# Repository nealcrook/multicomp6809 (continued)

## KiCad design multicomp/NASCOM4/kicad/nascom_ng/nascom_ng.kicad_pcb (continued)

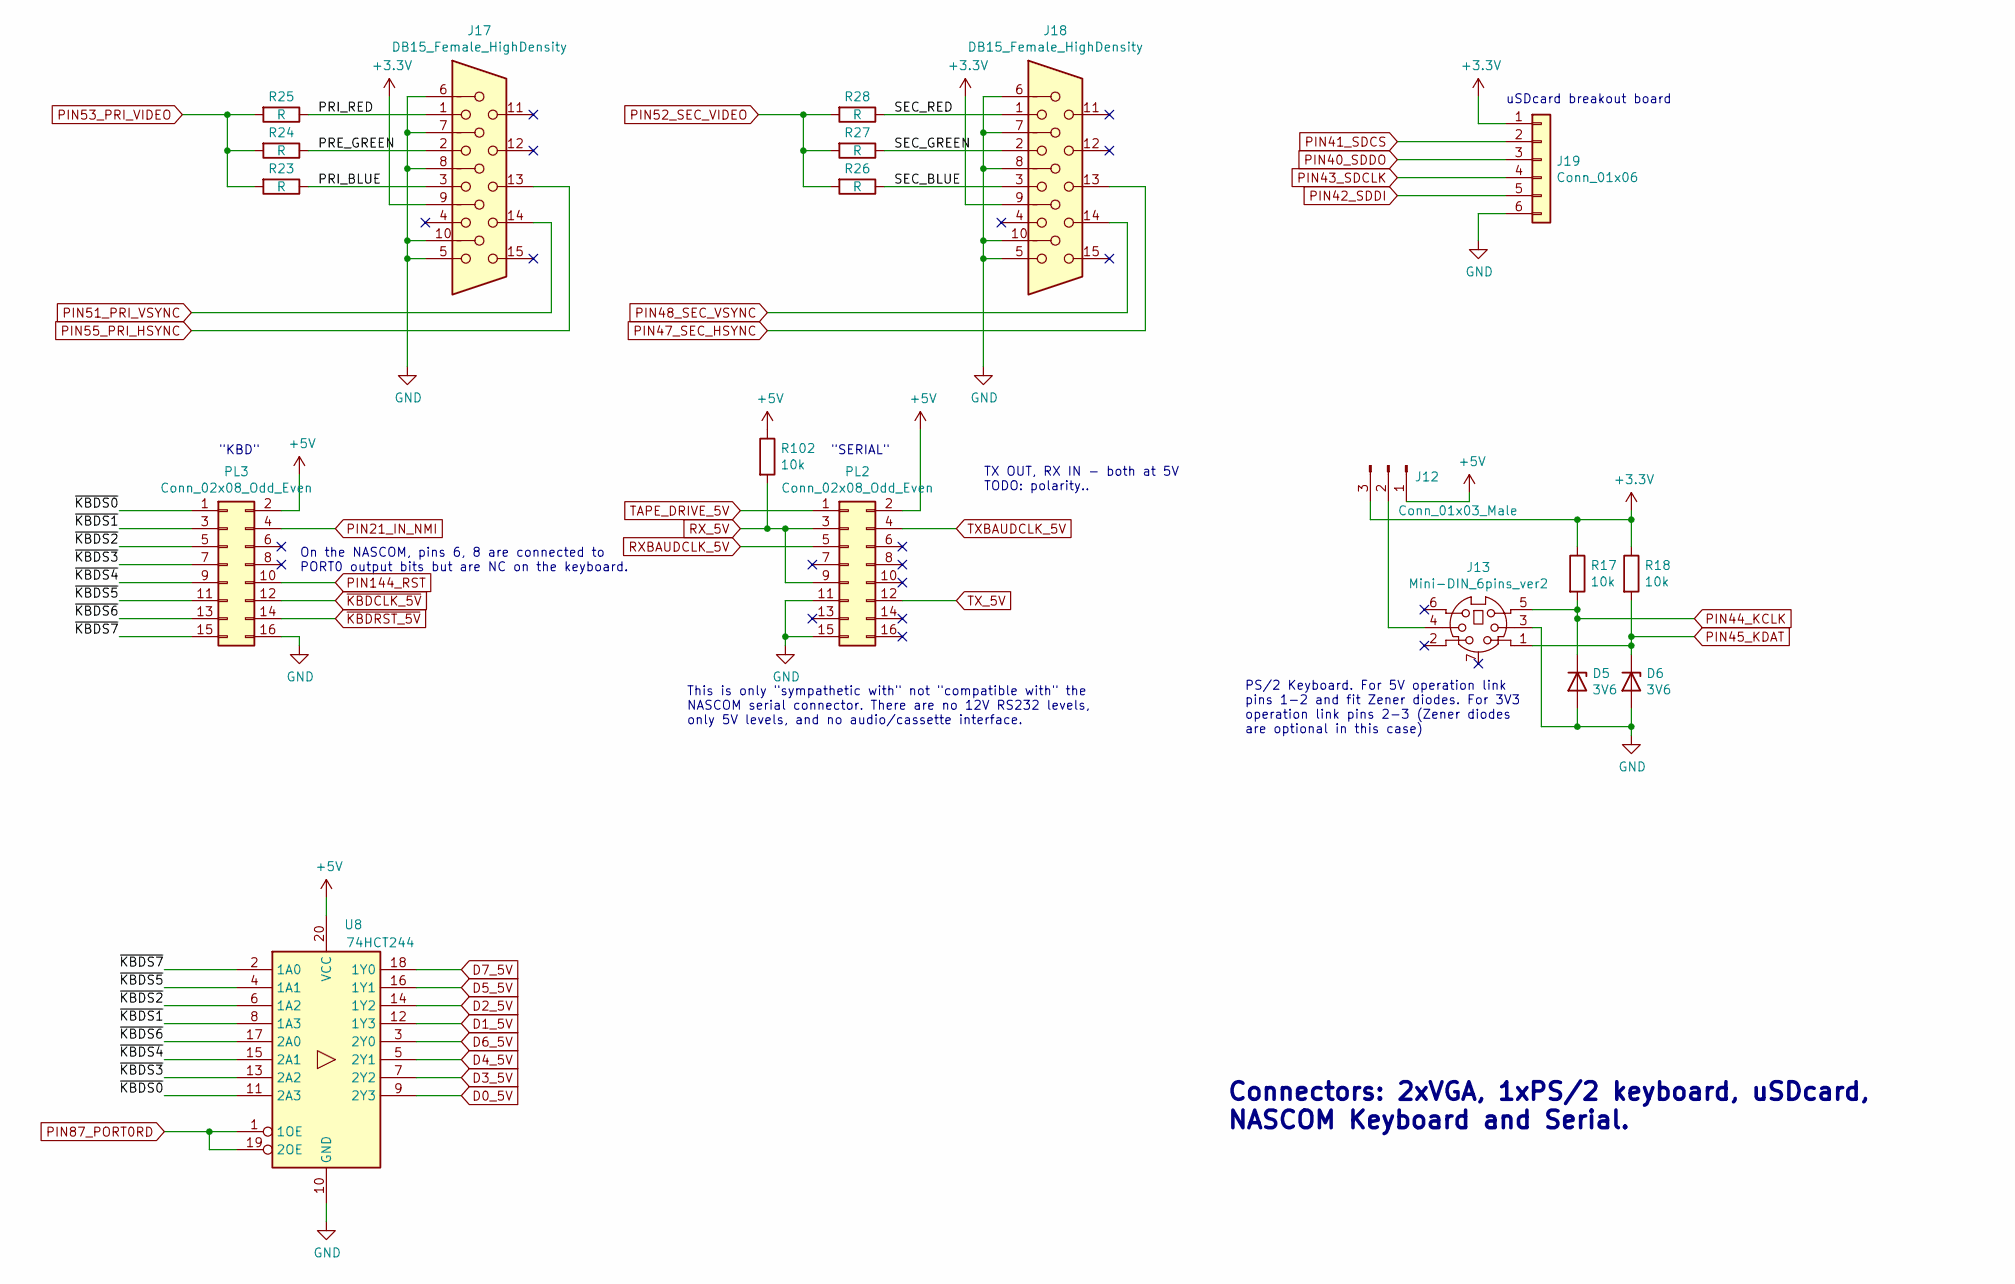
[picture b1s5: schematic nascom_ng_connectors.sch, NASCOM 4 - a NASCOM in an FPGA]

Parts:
D5, D6: 3V6; D_DO-35_SOD27_P7.62mm_Horizontal
J12: Conn_01x03_Male; PinHeader_1x03_P2.54mm_Vertical
J13: Mini-DIN_6pins_ver2; Connector_Mini-DIN_Female_6Pin_2rows
J17, J18: DB15_Female_HighDensity; DSUB-15-HD_Female_Horizontal_P2.29x1.98mm_EdgePinOffset3.03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
J19: Conn_01x06; uSDcard_breakout_1x06_P2.54mm
PL2, PL3: Conn_02x08_Odd_Even; IDC-Header_2x08_P2.54mm_Vertical
R17, R18, R102: 10k; R_Axial_DIN0204_L3.6mm_D1.6mm_P7.62mm_Horizontal
R23, R24, R25, R26, R27, R28: R; R_Axial_DIN0204_L3.6mm_D1.6mm_P7.62mm_Horizontal
U8: 74HCT244; DIP-20_W7.62mm

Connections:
+5V: J12.1, PL2.2, PL3.2, R102.1, U8.20 (VCC); also elsewhere on the board
/nascom_ng_connectors/PRE_GREEN: J17.2, R24.1
/nascom_ng_connectors/PRI_BLUE: J17.3, R23.1
/nascom_ng_connectors/PRI_RED: J17.1, R25.1
/nascom_ng_connectors/SEC_BLUE: J18.3, R26.1
/nascom_ng_connectors/SEC_GREEN: J18.2, R27.1
/nascom_ng_connectors/SEC_RED: J18.1, R28.1
/nascom_ng_connectors/~KBDS0: PL3.1, U8.11 (2A3)
/nascom_ng_connectors/~KBDS1: PL3.3, U8.8 (1A3)
/nascom_ng_connectors/~KBDS2: PL3.5, U8.6 (1A2)
/nascom_ng_connectors/~KBDS3: PL3.7, U8.13 (2A2)
/nascom_ng_connectors/~KBDS4: PL3.9, U8.15 (2A1)
/nascom_ng_connectors/~KBDS5: PL3.11, U8.4 (1A1)
/nascom_ng_connectors/~KBDS6: PL3.13, U8.17 (2A0)
/nascom_ng_connectors/~KBDS7: PL3.15, U8.2 (1A0)
D0_5V: U8.9 (2Y3); also elsewhere on the board
D1_5V: U8.12 (1Y3); also elsewhere on the board
D2_5V: U8.14 (1Y2); also elsewhere on the board
D3_5V: U8.7 (2Y2); also elsewhere on the board
D4_5V: U8.5 (2Y1); also elsewhere on the board
D5_5V: U8.16 (1Y1); also elsewhere on the board
D6_5V: U8.3 (2Y0); also elsewhere on the board
D7_5V: U8.18 (1Y0); also elsewhere on the board
GND: D5.2 (A), D6.2 (A), J13.3, J17.5, J17.6, J17.7, J17.8, J17.10, J18.5, J18.6, J18.7, J18.8, J18.10, J19.6, PL2.11, PL2.15, PL3.16, U8.10 (GND); also elsewhere on the board
unnamed: J12.2, J13.4
PIN21_IN_NMI: PL3.4; also elsewhere on the board
PIN40_SDDO: J19.3; also elsewhere on the board
PIN41_SDCS: J19.2; also elsewhere on the board
PIN42_SDDI: J19.5; also elsewhere on the board
PIN43_SDCLK: J19.4; also elsewhere on the board
PIN44_KCLK: D5.1 (K), J13.5, R17.2; also elsewhere on the board
PIN45_KDAT: D6.1 (K), J13.1, R18.2; also elsewhere on the board
PIN47_SEC_HSYNC: J18.13; also elsewhere on the board
PIN48_SEC_VSYNC: J18.14; also elsewhere on the board
PIN51_PRI_VSYNC: J17.14; also elsewhere on the board
PIN52_SEC_VIDEO: R26.2, R27.2, R28.2; also elsewhere on the board
PIN53_PRI_VIDEO: R23.2, R24.2, R25.2; also elsewhere on the board
PIN55_PRI_HSYNC: J17.13; also elsewhere on the board
PIN87_PORT0RD: U8.1 (1OE), U8.19 (2OE); also elsewhere on the board
PIN144_RST: PL3.10; also elsewhere on the board
RXBAUDCLK_5V: PL2.5; also elsewhere on the board
RX_5V: PL2.3, PL2.9, R102.2; also elsewhere on the board
TAPE_DRIVE_5V: PL2.1; also elsewhere on the board
TXBAUDCLK_5V: PL2.4; also elsewhere on the board
TX_5V: PL2.12; also elsewhere on the board
~KBDCLK_5V: PL3.12; also elsewhere on the board
~KBDRST_5V: PL3.14; also elsewhere on the board

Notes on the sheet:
PS/2 Keyboard. For 5V operation link pins 1-2 and fit Zener diodes. For 3V3 operation link pins 2-3 (Zener diodes are optional in this case)
On the NASCOM, pins 6, 8 are connected to PORT0 output bits but are NC on the keyboard.
"KBD"
"SERIAL"
This is only "sympathetic with" not "compatible with" the NASCOM serial connector. There are no 12V RS232 levels, only 5V levels, and no audio/cassette interface.
TX OUT, RX IN - both at 5V TODO: polarity..
uSDcard breakout board
Connectors: 2xVGA, 1xPS/2 keyboard, uSDcard, NASCOM Keyboard and Serial.

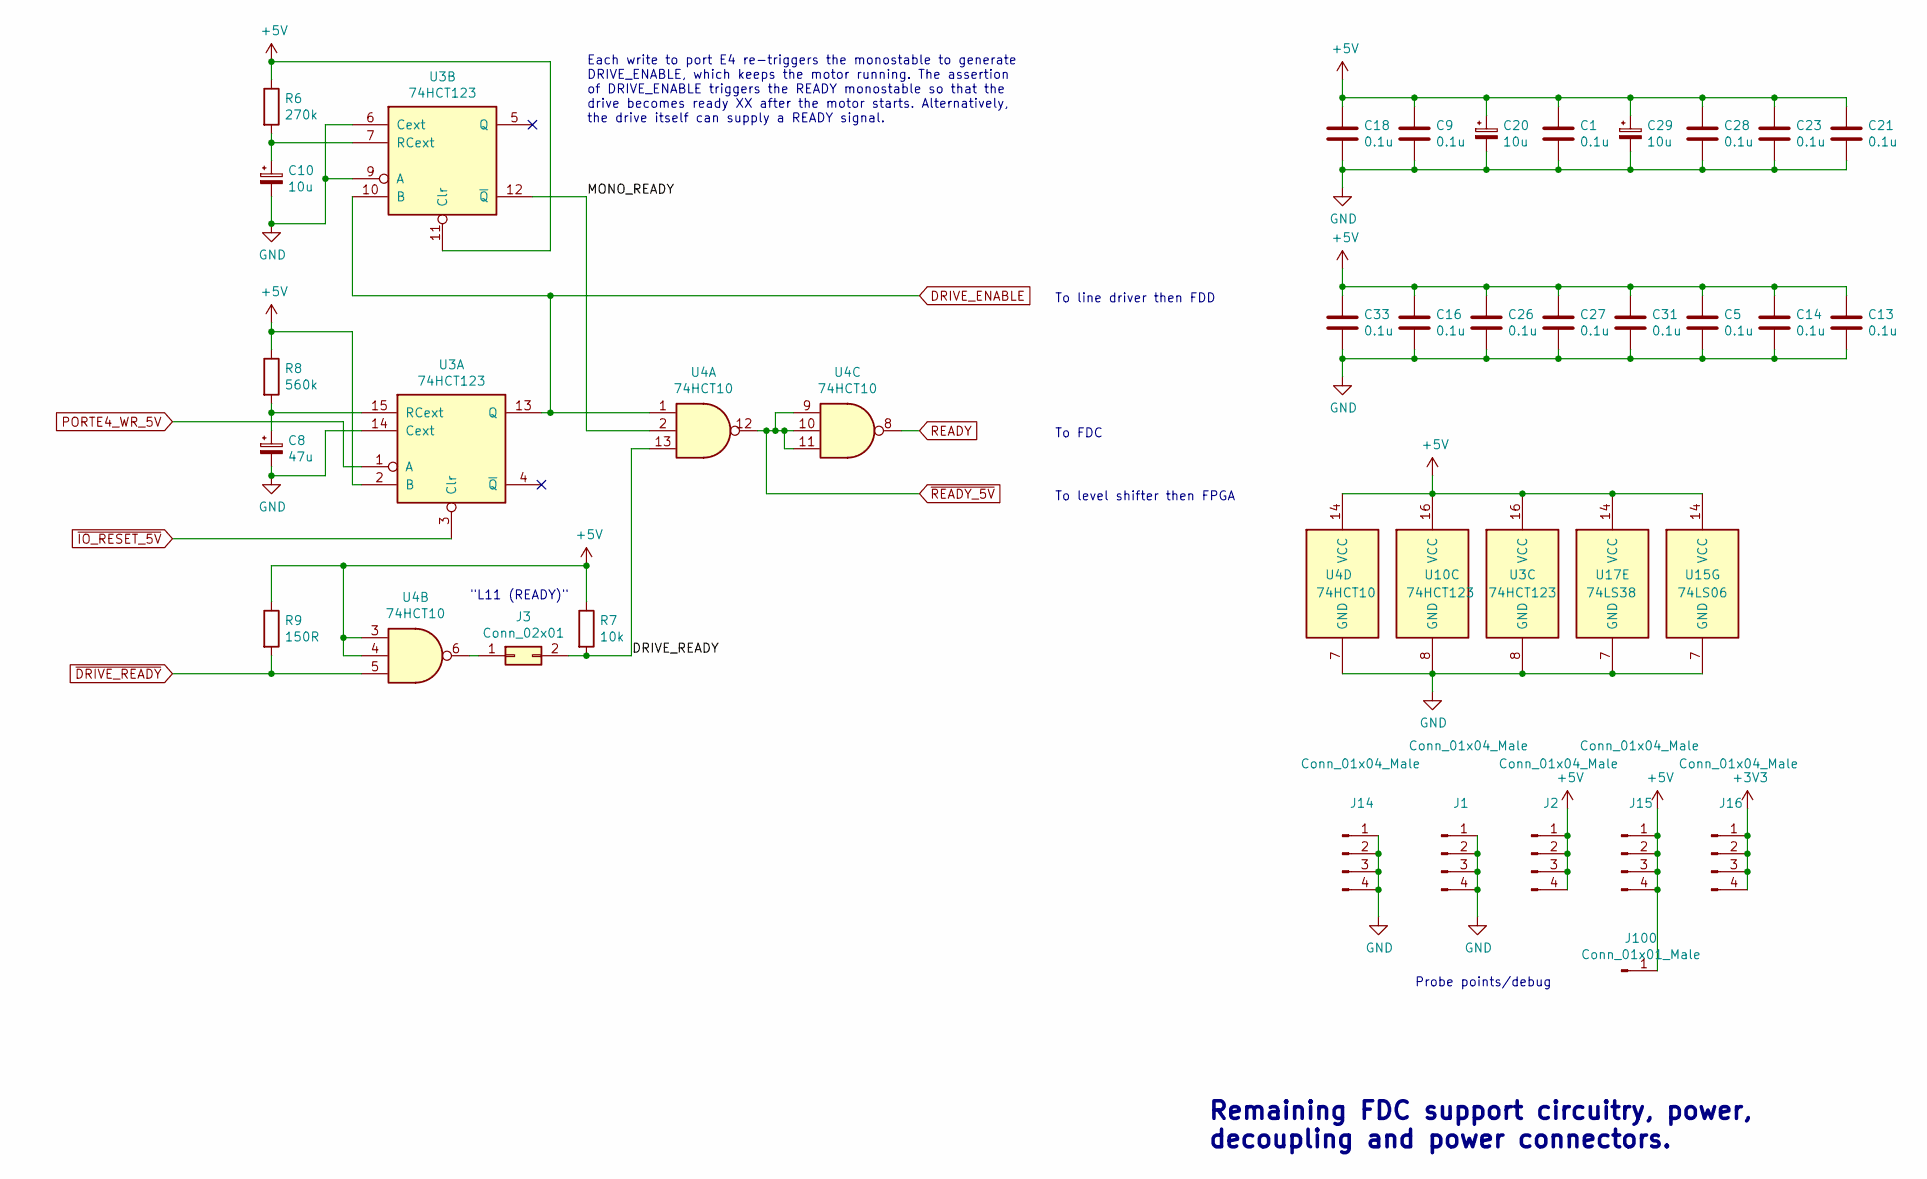
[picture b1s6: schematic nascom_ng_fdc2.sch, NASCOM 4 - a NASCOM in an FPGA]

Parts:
C1, C5, C9, C13, C14, C16, C18, C21, C23, C26, C27, C28, C31, C33: 0.1u; C_Disc_D3.0mm_W2.0mm_P2.50mm
C8: 47u; CP_Radial_Tantal_D4.5mm_P5.00mm
C10: 10u; CP_Radial_Tantal_D4.5mm_P5.00mm
C20, C29: 10u; CP_Radial_D5.0mm_P2.50mm
J1, J2, J14, J15, J16: Conn_01x04_Male; PinHeader_1x04_P2.54mm_Vertical
J3: Conn_02x01; PinHeader_2x01_P2.54mm_Vertical
J100: Conn_01x01_Male; PinHeader_1x01_P2.54mm_Vertical
R6: 270k; R_Axial_DIN0204_L3.6mm_D1.6mm_P7.62mm_Horizontal
R7: 10k; R_Axial_DIN0204_L3.6mm_D1.6mm_P7.62mm_Horizontal
R8: 560k; R_Axial_DIN0204_L3.6mm_D1.6mm_P7.62mm_Horizontal
R9: 150R; R_Axial_DIN0204_L3.6mm_D1.6mm_P7.62mm_Horizontal
U3, U10: 74HCT123; DIP-16_W7.62mm
U4: 74HCT10; DIP-14_W7.62mm
U15: 74LS06; DIP-14_W7.62mm
U17: 74LS38; DIP-14_W7.62mm

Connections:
+5V: C1.1, C5.1, C9.1, C13.1, C14.1, C16.1, C18.1, C20.1, C21.1, C23.1, C26.1, C27.1, C28.1, C29.1, C31.1, C33.1, J2.1, J2.2, J2.3, J2.4, J15.1, J15.2, J15.3, J15.4, J100.1, R6.1, R7.1, R8.1, R9.1, U3.2 (B), U3.11 (Clr), U3.16 (VCC), U4.3, U4.4, U4.14 (VCC), U10.16 (VCC), U15.14 (VCC), U17.14 (VCC); also elsewhere on the board
/nascom_ng_fdc2/DRIVE_READY: J3.2, R7.2, U4.13
/nascom_ng_fdc2/MONO_READY: U3.12 (~Q), U4.2
DRIVE_ENABLE: U3.10 (B), U3.13 (Q), U4.1; also elsewhere on the board
GND: C1.2, C5.2, C8.2, C9.2, C10.2, C13.2, C14.2, C16.2, C18.2, C20.2, C21.2, C23.2, C26.2, C27.2, C28.2, C29.2, C31.2, C33.2, J1.1, J1.2, J1.3, J1.4, J14.1, J14.2, J14.3, J14.4, U3.6 (Cext), U3.8 (GND), U3.9 (A), U3.14 (Cext), U4.7 (GND), U10.8 (GND), U15.7 (GND), U17.7 (GND); also elsewhere on the board
unnamed: C8.1, R8.2, U3.15 (RCext)
unnamed: C10.1, R6.2, U3.7 (RCext)
unnamed: J3.1, U4.6
PORTE4_WR_5V: U3.1 (A); also elsewhere on the board
READY: U4.8; also elsewhere on the board
~DRIVE_READY: R9.2, U4.5; also elsewhere on the board
~IO_RESET_5V: U3.3 (Clr); also elsewhere on the board
~READY_5V: U4.9, U4.10, U4.11, U4.12; also elsewhere on the board

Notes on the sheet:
"L11 (READY)"
Each write to port E4 re-triggers the monostable to generate DRIVE_ENABLE, which keeps the motor running. The assertion of DRIVE_ENABLE triggers the READY monostable so that the drive becomes ready XX after the motor starts. Alternatively, the drive itself can supply a READY signal.
To level shifter then FPGA
To FDC
To line driver then FDD
Remaining FDC support circuitry, power, decoupling and power connectors.
Probe points/debug

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
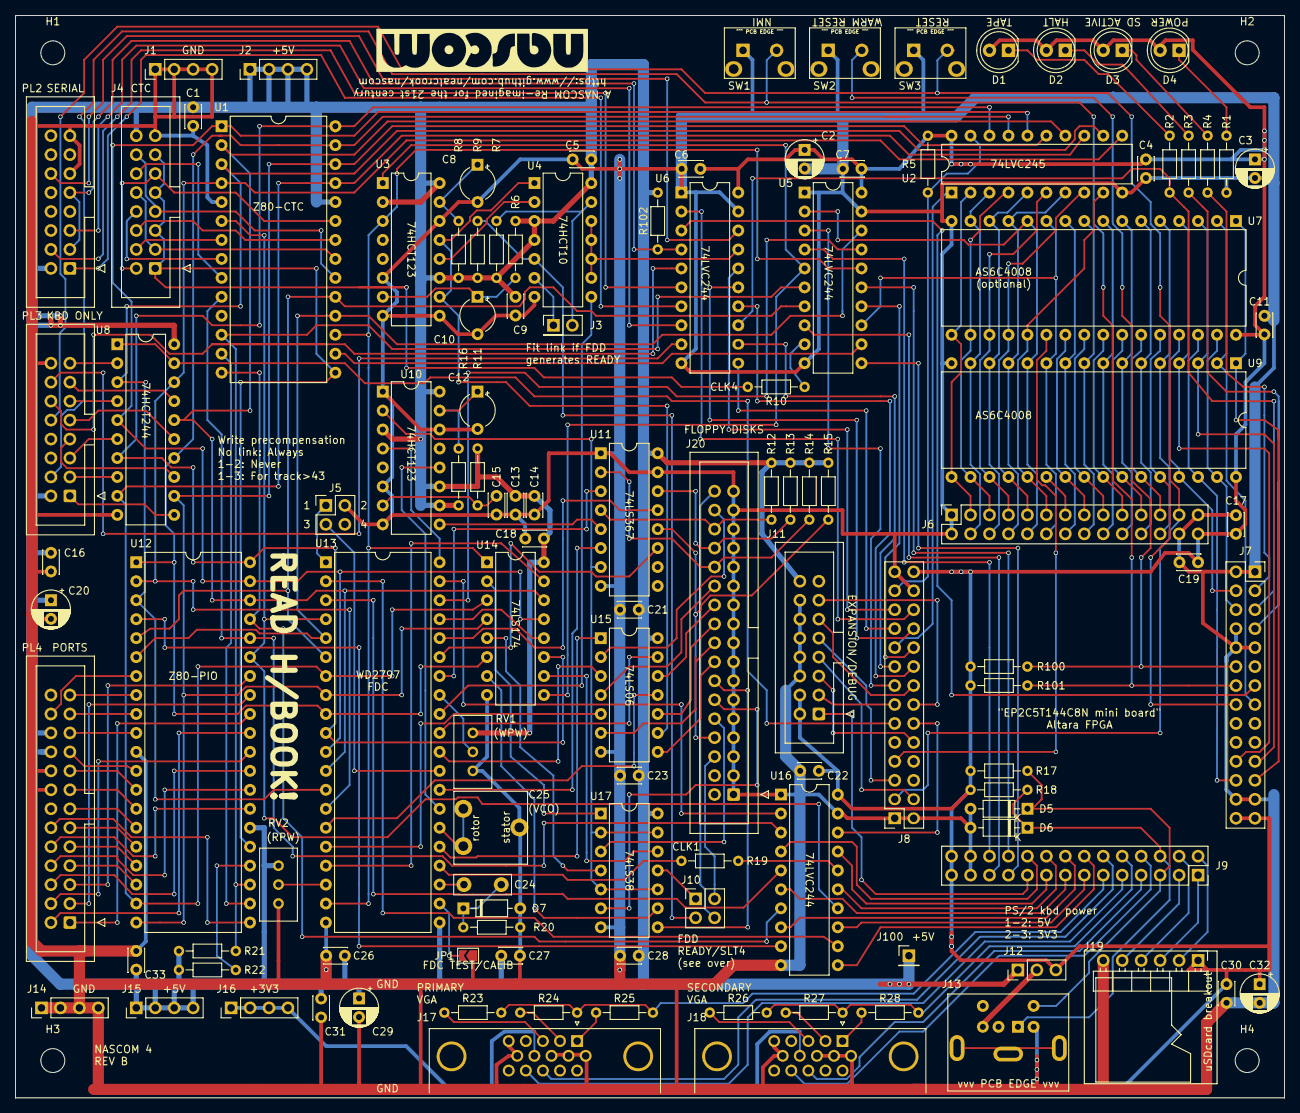
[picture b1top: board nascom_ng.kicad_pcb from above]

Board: 2 copper layers, 170.0 x 145.0 mm, 124 parts (0 on the bottom side), 218 nets.

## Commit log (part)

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2015-03-24 From cam09-10.zip
2015-03-24 116: Add .A and extend DUMP to print ASCII as well as hex 64, 77: Add HEX redundant but consistent 36, 37, 41: Change 2+ 2- to 2 + 2 - respectively so assembler can be read in by CamelForth itself.
2015-04-14 expand RAM space for multicomp. Add PICK (code definition) to code and documentation.
2015-05-10 reorganise structure ready for export to github.
2015-05-30 Add new word FLEX to boot FLEX operating system from SD card.
2015-05-31 on the way to the creation of a useful system disk image for porting. 1/ installed the multicomp boot loader on sector 0. It isn't usable in its current form because the tack/sector has not been patc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
2015-05-31 Tool for manipulating FLEX .dsk files
2015-06-11 Add SDcard block offsets for 4 drives.
2015-06-12 Accidentally specified a .dsk image that's bigger than 1.5Mbyte. Changed to a different one.
2015-06-23 Mk2 memory mapper, with capabilites for memory mapping and for the generation of a regular timer interrupt. Should meet the requirements for Level 1 and Level 2 port of NitrOS9.
2015-07-09 move all Flex dsk images to a single, better-named tree.
2015-07-13 Fix ROM part of address map for multicomp (to avoid I/O space). Patch in most of my changes from hack version. Patch in todo list.
2015-07-17 Fixed long-standing bug in SD driver; card could still be busy when new command is about to be issued; need to wait before issuing command. Now FLEX is far more reliable: the old problem that ICC cou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
2015-07-19 Add code to load and store sectors. Load and decode the SIR. Pretty- print the SIR as part of the info command output.
2015-07-20 abstract directory reading and call it at mount time. dir now can just apply a filter-by-name to that list.
2015-07-23 tidy up. Add FLEX constants, and use them. Pseudo-code for rm, cp. Refactor rd_sir more sensibly.
2015-08-10 Implement "scrub" command and its help.
2015-08-14 New FLEX disk with colossal cave adventure.
2015-08-16 oops. Commited by debug version. Really fixed now.
2015-08-17 export and list commands now working for text and raw binary. Added code to identify file type. Cleaned up pager and mechanism for switching between file handles. Converter for binary files and for h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
2015-08-23 patch in comments from old hacked version. Add label so that it assembles and links again.
2015-08-23 Fix zero-day bug with assembler error messages (caused lockup) Change all message strings from counted strings to null-terminated strings.
2015-08-26 switch to target-specific filename for nitos9 disk image.
2015-08-30 fix stupid typo in NITROS9: EF2CD instead of EFTOCD. The former is valid HEX so did not flag an error. No idea how I convinced myself it was working..
2015-09-22 No functional change. Two groups of syntax changes so that the design will load into modelsim without overflow error and without "Actual expression of formal is not globally static"
2015-09-22 No functional change. Delete trailing whitespace, add comments at start to describe programming model. Add comments to code. Name each process to aid in debug with the simulator.
2015-09-23 Add clock divider and generic that allows the divide value to be selected. Clock state machine on gated posedge clock.
2015-09-24 with recv_data and ocr_data merged into a single register, the separate state receive_ocr is no longer needed: receive_byte can perform both roles.
2015-10-04 photos of multicomp running flex and buggy.
2015-10-17 Rebuilt from sources under Mercurial revision control Renamed serial driver as mc6850 Added 2 serial ports T0 T1 as well as virtual UART "Term" that is used for boot.
2015-11-10 Original UART design
2016-01-01 Whitespace changes and comment fix-ups; no functional changes.
2016-01-09 Simple script to create a release SDcard image for retrobrewcomputers.org
2016-01-17 Expand blocks file from 240 to 256 screens. No screen references change. Moved around the stuff in the multicomp screens to make space for additional SDcard words. Overall, no functional changes and 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
2016-01-29 do the checksum per-line and per-block rather than simply per-block; only doing it per-block makes the output noisy on a diff and makes it trickier by inspection to see what's changed.
2016-02-04 add change history
2016-02-05 Note revision of CUBIX page and introduction of cubix_autoboot.asm
2016-02-13 Update README.
2016-02-24 Change "2 +" to CELL+ in 6809 assembler word IMMED. This is needed for portability; without this fix, IMMED misbehaves when the host (the environment in which the assembler runs) is anything other th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
2016-02-24 Add ANS BLOCK/BLOCK EXT words:
    Screen 125, 126:
    helper words
    Screen 127:
    ANS Standard words
    Currently the standard words are mis-named (their initial letters are X) to
    avoid a clash with the metacompiler. I think I know how to fix this now..
2016-02-26 Overhaul the comments in the shadow screens. No change to generated binary.
2016-03-17 Add dialogue on status line for save/discard edits and move x-out dialogue to status line. New behaviour stops edits from being lost when you skip backwards and forwards to different blocks. Change a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
2016-03-20 reformat slightly so it fits on 2 pages again.
2016-03-25 revise values to match latest build. Add :NONAME and thoughts on how it might look (not currently part of CamelForth).
2016-05-11 Add FUZIX word to F83 version and ANS version. Commit ANS version for the first time - though it's not completely finished it does create identical code to the F83 version for the current Chromium so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
2016-05-11 rework diagrams to appear properly in ASCII
2016-06-11 Tweak keyboard mapping so that ESC key generates 0x1b (escape).
2016-09-28 Add waves showing CPU clock control
2016-10-22 Make 'mount' work harder to recognise disk/image format - recognises dsk DSK Dsk etc. all as dsk image format.
2016-10-28 First working version of import command. Only words with default, raw format at the moment.
2016-10-31 Be more consistent in file naming.
2016-11-03 Revamped date handling: - Set session date from host system at startup. - New 'date' command allows arbitrary date to be set. Date is used for 'import' and 'new' commands 'label' command still suppor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
    Added some testing of dates to make sure each element is in range (no check
    that the day/month/year is consistent, though).
    Changed to use of mm,dd,yy format, to match Flex DATE command (previously
    used mm/dd/yy).
    Reviewed all year stuff for Y2K compliance - which simply meant ensuring that
    the year is in the range 0-99.
2016-11-08 Implement better checking for extra (and illegal) arguments on the command line Refer to FLEX as FLEX and not Flex (revert ill-considered change from last week) Add "compress" capability to import co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
2016-11-10 The 'import' command should now be fully functional. It now does better checking of files pre=-import, elimimating those with illegal names and zero file size. It also looks for pre-existing files of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
2016-11-13 Update system disk: Move from FLEX 9.0 to FLEX 9.1 Changed a bunch of the utilities to versions rebuilt from source Replaced DATE with a Y2K-clean version. Added new disk image multicomp09_flexsrc.ds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
2016-11-14 Disk images for scratch disks.
2016-11-16 Make drive 2 the new flexsrc disk - utilities and other source code. Reference all of the FLEX files in the ../flex directory.
2016-11-24 script to ease the construction of a release image of the SD card.
2016-12-01 script to replace nitros disk3
2017-04-22 Up-size the blank disks to be as big as they can be without messing up the SDcard layout.
2017-06-02 NitrOS-9 code is now in the official repository on sourceforge, so retire the old Level 1 disk image.
2017-09-05 Convert an Intel HEX file to a format where it can be included as data in a C program.
2018-08-10 Remove trailing whitespace and non-ASCII characters from basic.asm. Assembled image is identical.
2018-08-10 Superceeded by make_sd_release.
2019-03-20 Script to create a zip file of the FPGA stuff.
2020-05-23 two completely empty block files - used by the SDcard build script.
2020-05-24 Just fixed FULL? in chromium.scr - I had previously implemented a bad fix for that problem here. Now I've implemented the same, good fix as in chromium.scr
2020-07-19 report file size mismatches in a more useful way.
2020-08-02 Add 'rattle' and 'chain' commands for inspecting chains of sectors and the links in them. Change the way that track/sectors are entered and reported to be shorter and consistent. Change edlink to rep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
2020-08-09 new 'hash' command for reporting MD5SUM of a file payload.
2020-11-18 Add MREQ to memory write decode. Connect NMI. Code Port0-controlled single-step logic.
2020-11-23 Add VFC ROM and special boot ROM. Add decoding to page out NASCOM stuff and page in VFC stuff.
2020-12-05 Video: All static configuration to disable the cursor. Delete unused signals UART: new UART 6402-like. Top: instance new UART. Add static configuration to switch between real UART (for FPGA testing) 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
2020-12-12 Implement menu-based system for choosing startup environment.
2020-12-25 Load profile into video RAM instead of C80. This allows programs to be loaded at C80 (eg M5 or David's memory test). Inhibit writes to SRAM when video RAM or workspace RAM are decoded: bugs found by 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
2021-01-17 Move @ key and add :/* key, previously missing. Add notes on fn key support - not yet implemented.
2021-01-27 Remove bootmode pins in favour of a more flexible and simpler cold/warm reset managed by SBootROM. Add POR and reason registers; the reason register will get more functionality once the keyboard func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
2021-03-03 Formatting and comment changes, remove use of SCAL macro (makes it more likely to assemble with Osonsoft tools). Binary is identical to previous version.
2021-03-07 Connect pin as CPU interrupt for debug of bridge logic. Recode io and dummy/m1 cycle in bridge.
2021-03-21 First version configured to run on the NASCOM4 PCB. Basic operation with SDcard, VGA, PS/2 keyboard, external RAM, LEDs working.
2021-04-03 Add optional data inversion on UART, controlled through port $1D. This allows nascom_sdcard to be used without modification. Change register $1D to not be reset but to have its default established in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
2021-04-11 no functional change, just tidy-up of indent (remove tab, move to consistent 4-space indent style).
2021-04-18 Fix debounce on NMI. Swap ports EE/EF back - previous change stopped MAP80 CP/M 2.2 from booting properly, because that code was switching to the NASCOM screen after boot. Start of logic for MC6845 c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
2021-05-22 Update adventure.dsk
    Fixed the bug in saving and loading
    Implementation is in
    https://github.com/prasys/ADVENT-Flex
2021-11-21 Make character generator programmable; mapped into VFC 4K region and enabled by port18 bit 7. Worked example in Handbook.
2022-01-13 Sources for VED2; versions for FLEX and for Linux
2022-12-03 Rebuild for Rev1.3 -- add pull-ups to some pins so that depopulated builds don't leave floating inputs to the FPGA (which cause misoperation, eg chattering UART input).
2023-11-07 Add readline (Command recall/auto-completion) support.
2023-11-25 remove {dir} data structure from $dsk. Now, the data structure is created on-demand as a transient blob of data. This is less efficient but (1) it avoids the need for cache_dir() to refresh the data 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
